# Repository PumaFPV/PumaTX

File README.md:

# PumaTX

THIS README IS NOT UP TO DATE

# Introduction:
This is a try to build my own FPV remote controller based on ESP32 (nRF52 later on) and DJI GL200A for its compactness and format.

# Release Candidates:

RC04: 
	Software:
		PPM
		SBus
		Hall Effect
		Pots reading (Left pot mode switch left = down ; Right = up ; RTH = overwrite)
		Arm reading
		Pre reading
		RTH reading
		Power on / off via sport switch
		basic screen use + vbat + splash screen
		
	Hardware:
		Micro USB (from controller)
		2S LiPo
		external RF (R9M)
		USB 2.0 (or 3.0 if I find one,) to plug in module (gnd, 5v, VBat, Tx)
		Support for JR module in phone holder
		
RC05:
	Software:
		Interupts for buttons (so code can run faster)
		MavLink (only rc, no telemetry) 
§		MavLink Bluetooth Passthrough (Uses to much memory, will have to sort it out for another release)
§		Choice between SBus and MavLink when compiling
		SoftPower use only interrupt
§		LED for power
		
	Hardware:
§		1S battery + USB charger + boost converter
§		MavLink module
		
RC06:
	Software:
		Menu Navigation
		
	Hardware:
		Turn on / off stuff (transistor & MOSFET)
		Fan
		Haptic
		
RC07:
	Software:
		Bluetooth HID
		
RC08:
	Software:
		MavLink telemetry screen

RC09:
	Software:
		CVBS Screen
		
	Hardware:
		USB 3.0 (5v, gnd, tx, rx, vid, 1, 2, VBat)
	
RC10:
	Hardware:
		Homemade PCB
		C1, C2
		Haptic
		
Other ideas:
	SPort
	FrSky X for bind / Rx num
	Sound output
	External bluetooth joystick
	Fix the calibration issue
	Remove screen loop
	eepron save
	
# Required specs:
-Read data from the hall effect MLX sensors from the controller

-Have 10 channels (can't do more cause of the limitation of the controller)

-Output SBus (to plug into R9M)

-Input SPort to read telemetry data (From R9M)

-Have a screen for minimal setup

-Have a Soft Power capabilty (using the power button from the controller)

This is the bare minimum. But I do have way more ideas coming.

# Folders:
In the "PumaTX_RC" folder you will find the different Release Candidate (Higher is better but could be unstable, read description for more details).

In the "Other" folder you will find different kind of "documentation" it is mostly here for my personnal use, as a reference.

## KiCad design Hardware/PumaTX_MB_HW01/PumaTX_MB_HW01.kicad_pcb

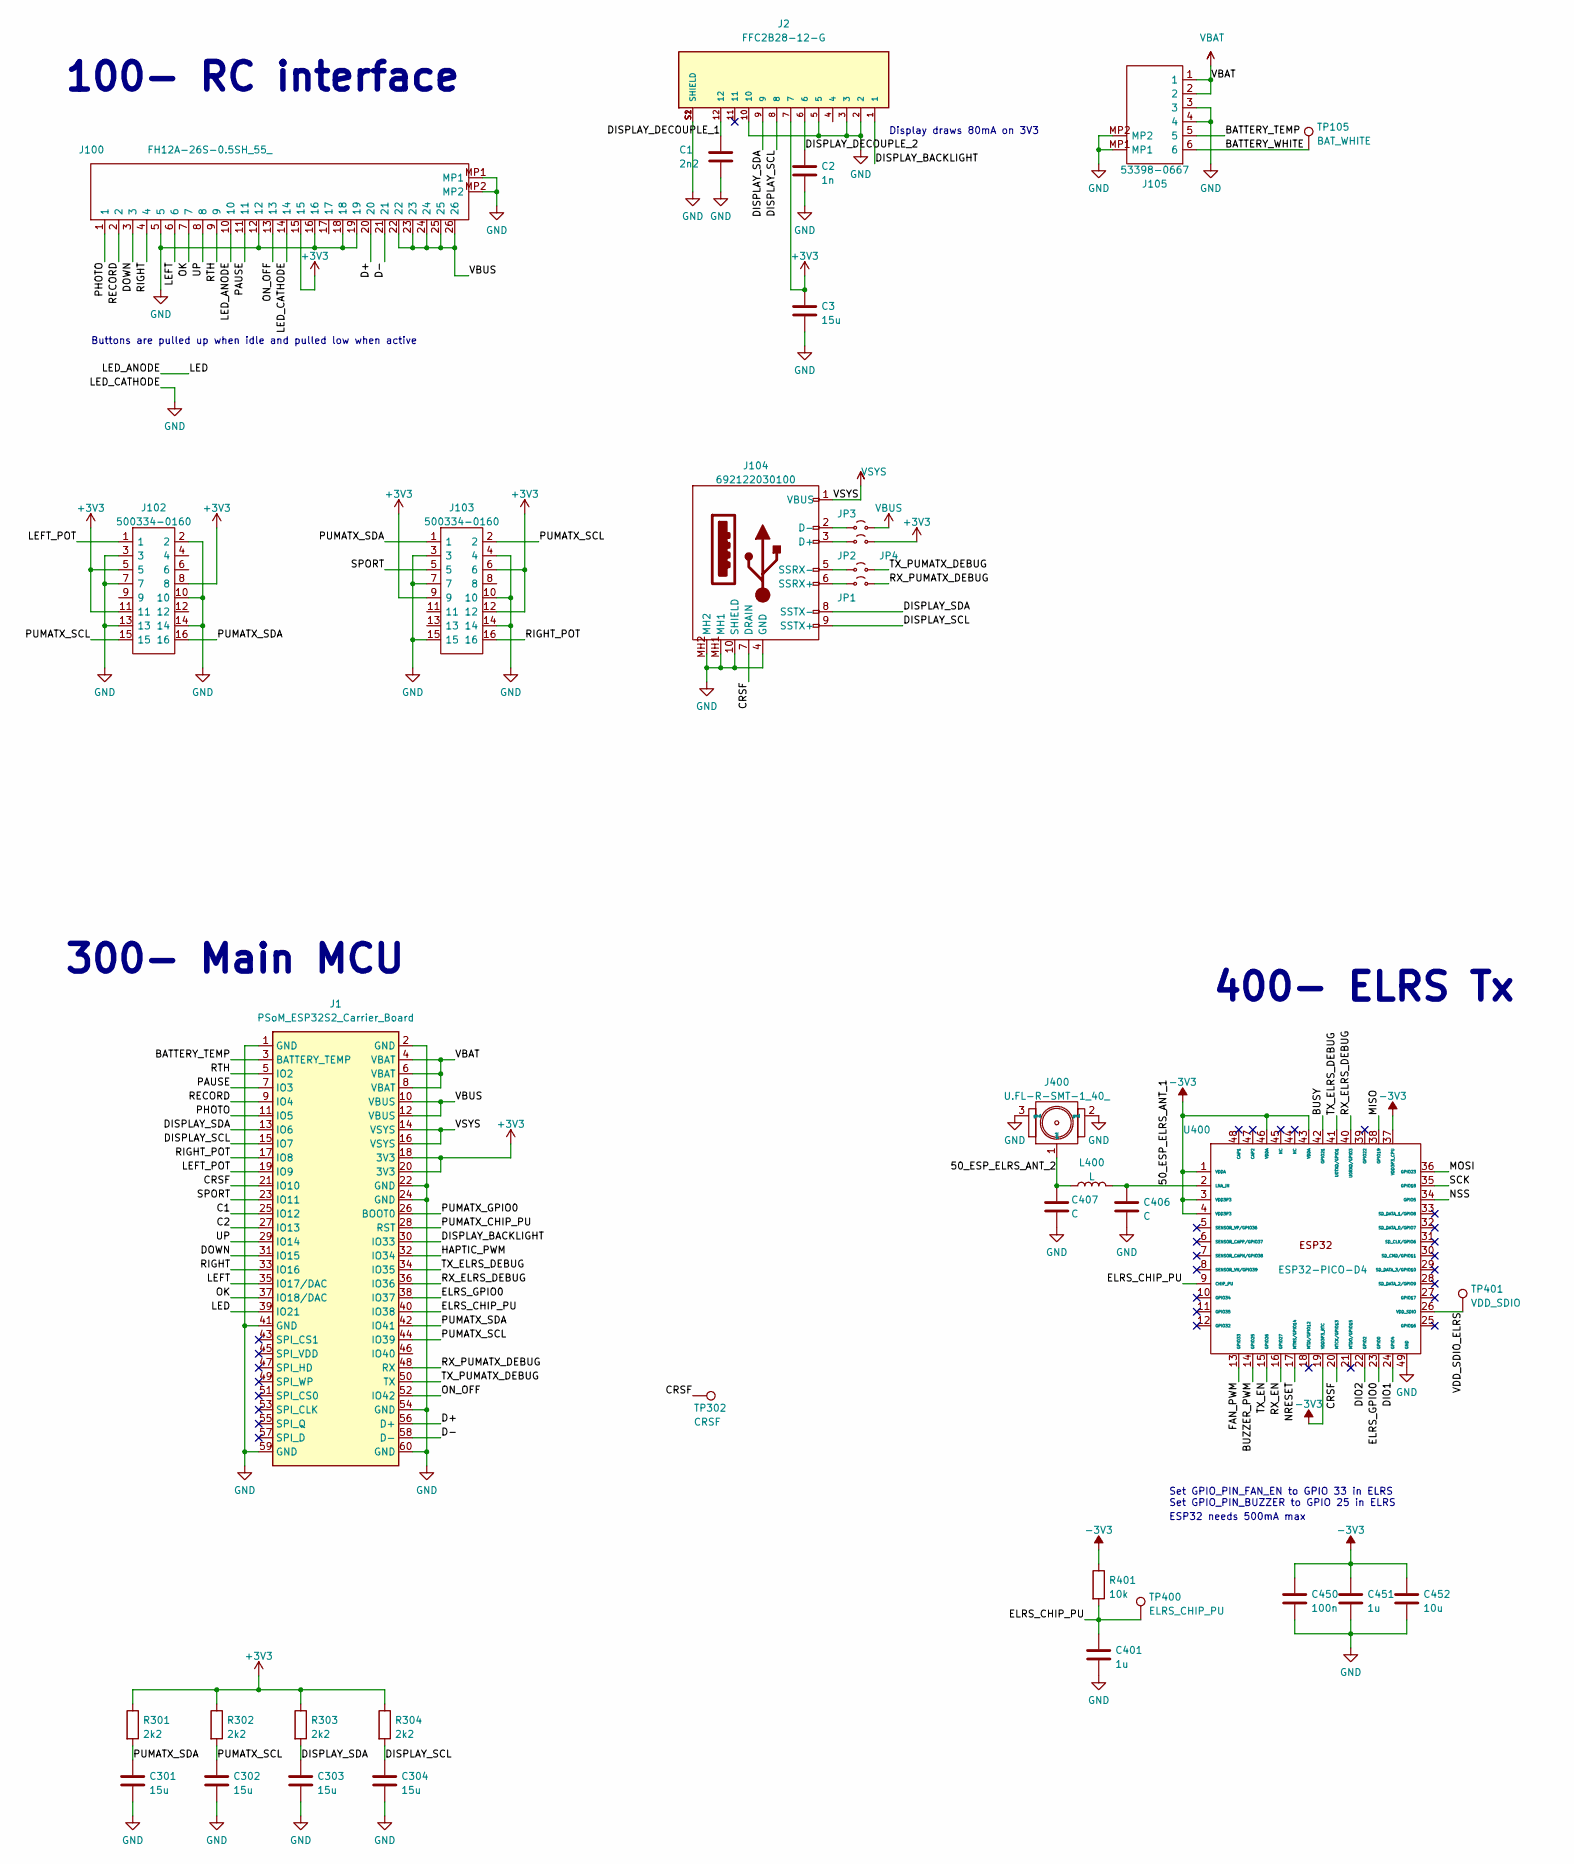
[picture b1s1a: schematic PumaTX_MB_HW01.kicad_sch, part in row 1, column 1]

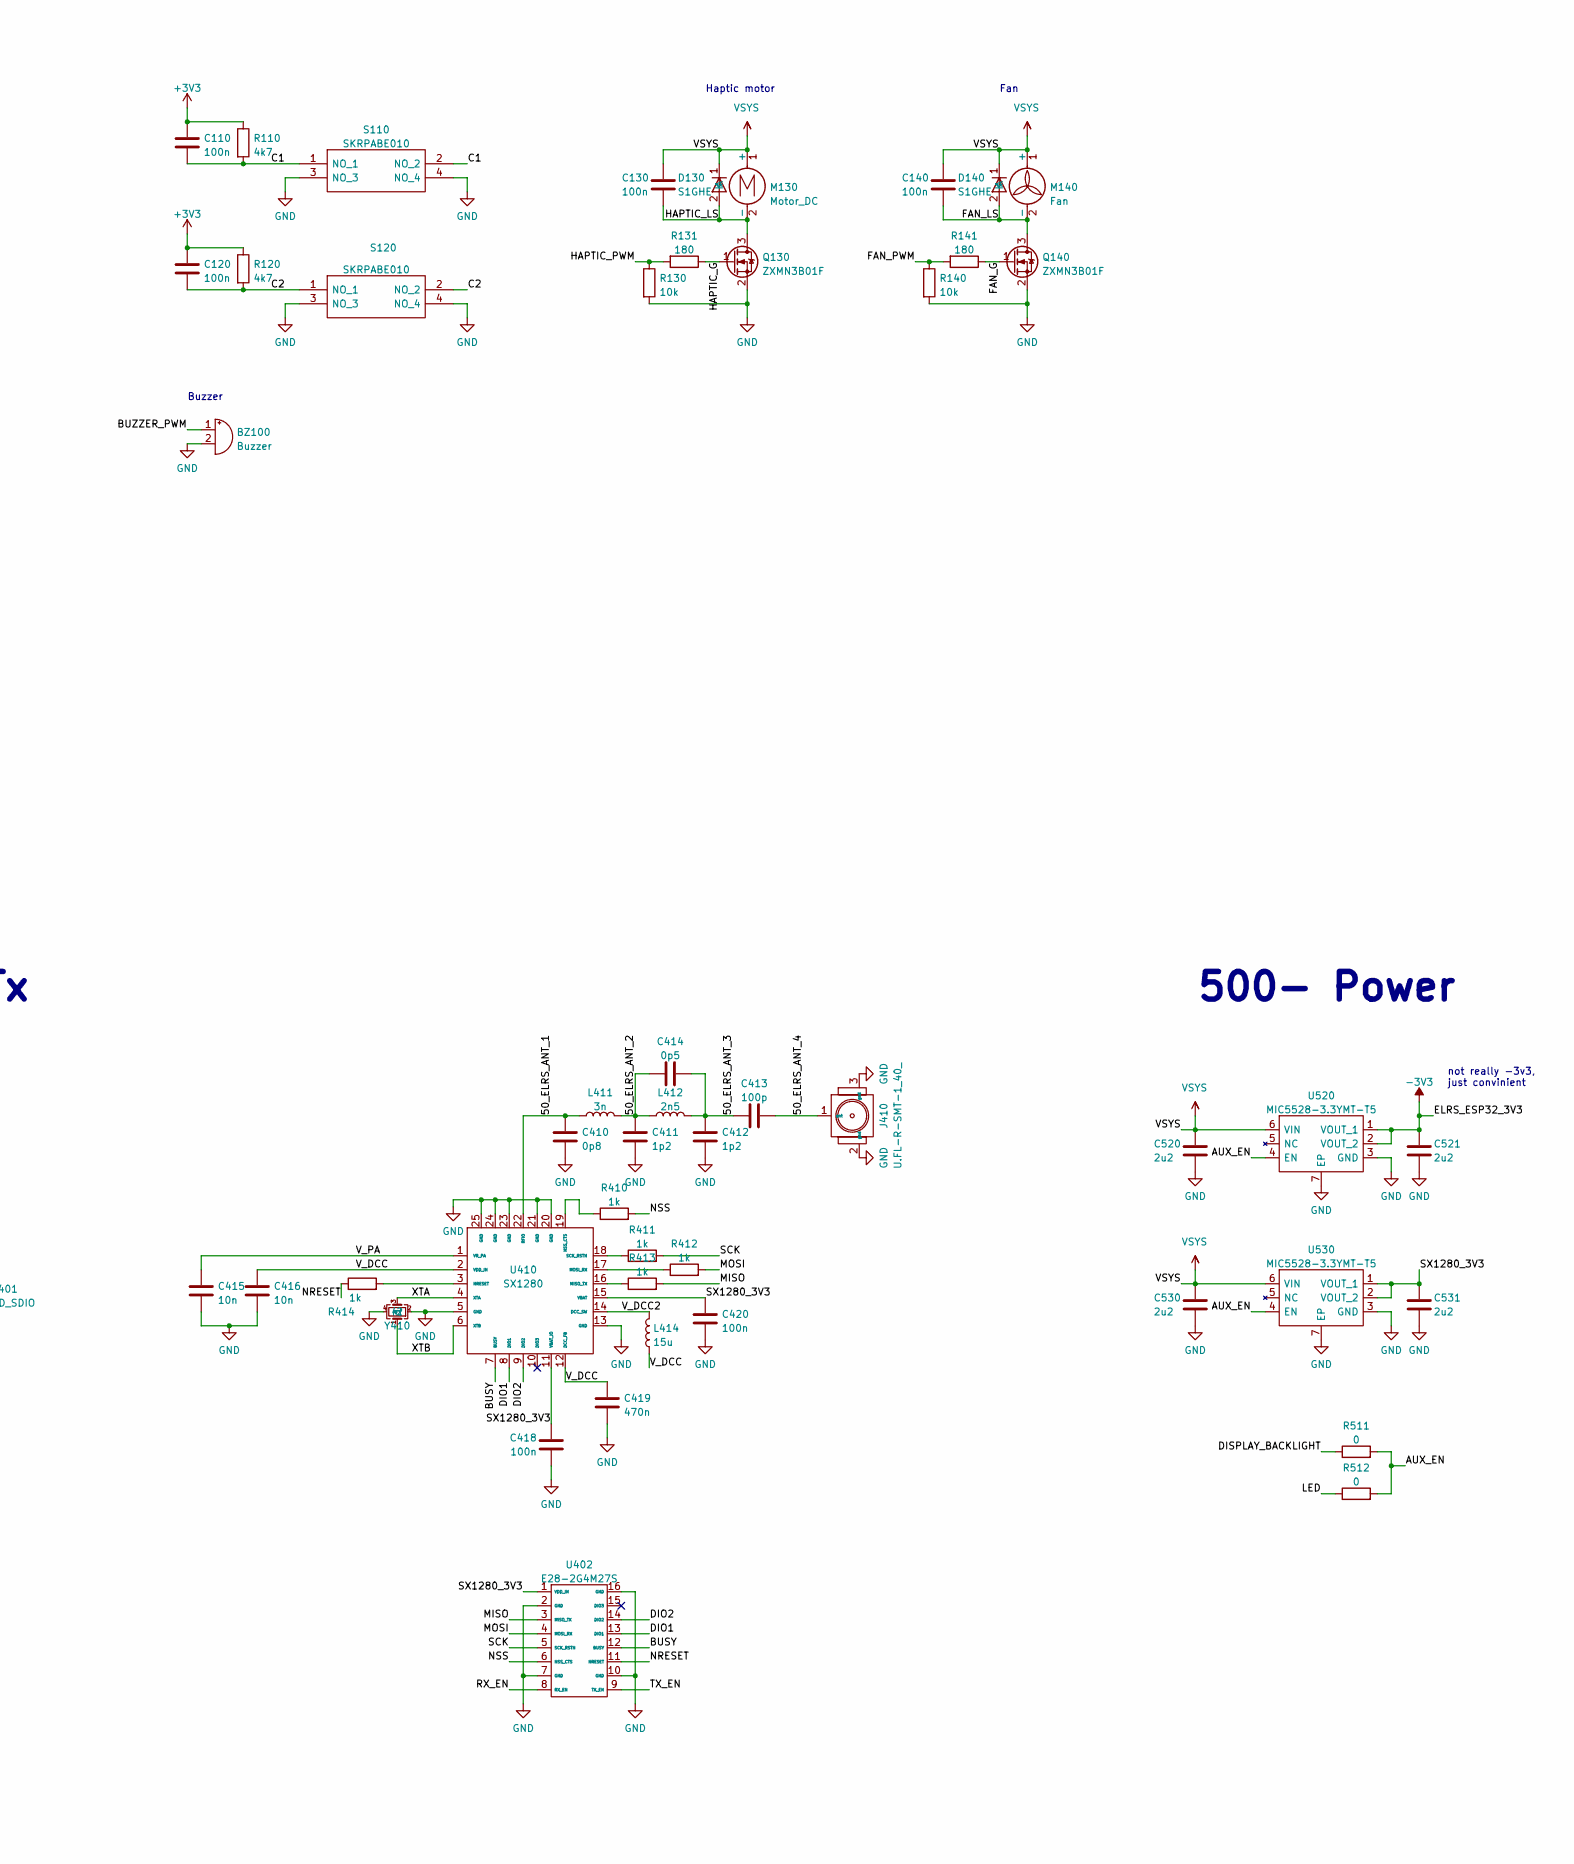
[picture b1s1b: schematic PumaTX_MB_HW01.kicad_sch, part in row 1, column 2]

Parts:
BZ100: Buzzer; GL200A_BUZZER
C1: 2n2; C_0402_1005Metric
C2: 1n; C_0402_1005Metric
C3, C301, C302, C303, C304: 15u; C_0402_1005Metric
C110, C120, C130, C140, C418, C420, C450: 100n; C_0402_1005Metric
C401, C451: 1u; C_0402_1005Metric
C406, C407: C; C_0201_0603Metric
C410: 0p8; C_0201_0603Metric
C411, C412: 1p2; C_0201_0603Metric
C413: 100p; C_0201_0603Metric
C414: 0p5; C_0201_0603Metric
C415, C416: 10n; C_0402_1005Metric
C419: 470n; C_0603_1608Metric
C452: 10u; C_0402_1005Metric
C520, C521, C530, C531: 2u2; C_0603_1608Metric
D130, D140: S1GHE; Mouser Part Number 512-S1GHE
J1: PSoM_ESP32S2_Carrier_Board; PSoM_ESP32S2_00
J2: FFC2B28-12-G; GCT_FFC2B28-12-G; PARTREV A; DigiKey_Part_Number 2073-FFC2B28-12-GTR-ND
J100: FH12A-26S-0.5SH_55_; FH12A26S05SH55; Mouser Part Number 798-FH12A-26S0.5SH55
J102, J103: 500334-0160; 5003340160; Mouser Part Number 538-500334-0160
J104: 692122030100; Mouser Part Number 710-692122030100
J105: 53398-0667; 533980667; Mouser Part Number 538-53398-0667
J400, J410: U.FL-R-SMT-1_40_; u.fl; Mouser Part Number 798-UFLRSMT140
JP1, JP2, JP3, JP4: Jumper_2_Small_Open; SolderJumper-2_P1.3mm_Open_RoundedPad1.0x1.5mm
L400: L; C_0402_1005Metric
L411: 3n; C_0402_1005Metric
L412: 2n5; C_0402_1005Metric
L414: 15u; C_0805_2012Metric
M130: Motor_DC; GL200A_HAPTIC_MOTOR
M140: Fan; SM02B-SURS-TF
Q130, Q140: ZXMN3B01F; SOT-23
R110, R120: 4k7; C_0402_1005Metric
R130, R140: 10k; C_0402_1005Metric
R131, R141: 180; C_0402_1005Metric
R301, R302, R303, R304: 2k2; C_0201_0603Metric
R401: 10k; C_0201_0603Metric
R410, R411, R412, R413, R414: 1k; C_0201_0603Metric
R511, R512: 0; C_0201_0603Metric
S110, S120: SKRPABE010; Mouser Part Number 688-SKRPAB
TP105: BAT_WHITE; TestPoint_Pad_D1.0mm
TP302: CRSF; TestPoint_Pad_D1.0mm
TP400: ELRS_CHIP_PU; TestPoint_Pad_D1.0mm
TP401: VDD_SDIO; TestPoint_Pad_D1.0mm
U400: ESP32-PICO-D4; ESP32-PICO-D4_1; Mouser Part Number 356-ESP32-PICO-D4
U402: E28-2G4M27S
U410: SX1280; QFN50P400X400X100-25N-D
U520, U530: MIC5528-3.3YMT-T5; SON40P120X120X60-7N-D; Mouser Part Number 998-MIC5528-3.3YMTT5
Y410: NX2016SA-52MHZ-EXS00A-CS06016; NX2016SA32MEXS00ACS06465; Mouser Part Number NX2016SA-52MHZ-EXS00A-CS06016

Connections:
+3V3: C3.1, C110.1, C120.1, J1.18 (3V3), J1.20 (3V3), J2.7, J100.15, J102.5, J102.8, J102.11, J103.6, J103.9, J103.12, JP4.2 (B), R110.1, R120.1, R301.1, R302.1, R303.1, R304.1; also elsewhere on the board
-3V3: C450.1, C451.1, C452.1, C521.1, R401.1, U400.1 (VDDA), U400.3 (VDD3P3), U400.4 (VDD3P3), U400.19 (VDD3P3_RTC), U400.37 (VDD3P3_CPU), U400.43 (VDDA), U400.46 (VDDA), U520.1 (VOUT_1), U520.2 (VOUT_2)
/50_ELRS_ANT_1: C410.1, L411.1, U410.22 (RFIO)
/50_ELRS_ANT_2: C411.1, C414.1, L411.2, L412.1
/50_ELRS_ANT_3: C412.1, C413.1, C414.2, L412.2
/50_ELRS_ANT_4: C413.2, J410.1 (ant)
/50_ESP_ELRS_ANT_1: C406.1, L400.2, U400.2 (LNA_IN)
/50_ESP_ELRS_ANT_2: C407.1, J400.1 (ant), L400.1
/AUX_EN: R511.2, R512.2, U520.4 (EN), U530.4 (EN)
/BATTERY_TEMP: J1.3 (BATTERY_TEMP), J105.5
/BATTERY_WHITE: J105.6, TP105.1
/BUSY: U400.42 (GPIO21), U402.12 (BUSY), U410.7 (BUSY)
/BUZZER_PWM: BZ100.1 (-), U400.14 (GPIO25)
/C1: C110.2, J1.25 (IO12), R110.2, S110.1 (NO), S110.2 (NO)
/C2: C120.2, J1.27 (IO13), R120.2, S120.1 (NO), S120.2 (NO)
/CRSF: J1.21 (IO10), J104.7 (DRAIN), TP302.1, U400.20 (MTCK/GPIO13)
/D+: J1.56 (D+), J100.20; also elsewhere on the board
/D-: J1.58 (D-), J100.21; also elsewhere on the board
/DIO1: U400.24 (GPIO4), U402.13 (DIO1), U410.8 (DIO1)
/DIO2: U400.22 (GPIO2), U402.14 (DIO2), U410.9 (DIO2)
/DISPLAY_BACKLIGHT: J1.30 (IO33), J2.1, R511.1
/DISPLAY_DECOUPLE_1: C1.1, J2.12; also elsewhere on the board
/DISPLAY_DECOUPLE_2: C2.1, J2.6; also elsewhere on the board
/DISPLAY_SCL: C304.1, J1.15 (IO7), J2.8, J104.9 (SSTX+), R304.2
/DISPLAY_SDA: C303.1, J1.13 (IO6), J2.9, J104.8 (SSTX-), R303.2
/DOWN: J1.31 (IO15), J100.3; also elsewhere on the board
/ELRS_CHIP_PU: C401.1, J1.40 (IO38), R401.2, TP400.1, U400.9 (CHIP_PU)
/ELRS_GPIO0: J1.38 (IO37), U400.23 (GPIO0)
/FAN_G: Q140.1 (G), R141.1
/FAN_LS: C140.1, D140.2 (A), M140.2 (-), Q140.3 (D)
/FAN_PWM: R140.1, R141.2, U400.13 (GPIO33)
/HAPTIC_G: Q130.1 (G), R131.1
/HAPTIC_LS: C130.1, D130.2 (A), M130.2 (-), Q130.3 (D)
/HAPTIC_PWM: J1.32 (IO34), R130.1, R131.2
/LED: J1.39 (IO21), J100.10, R512.1; also elsewhere on the board
/LEFT: J1.35 (IO17/DAC), J100.6; also elsewhere on the board
/LEFT_POT: J1.19 (IO9), J102.1
/MISO: R413.2, U400.38 (GPIO19), U402.3 (MISO_TX)
/MOSI: R412.2, U400.36 (GPIO23), U402.4 (MOSI_RX)
/NRESET: R414.1, U400.17 (MTMS/GPIO14), U402.11 (NRESET)
/NSS: R410.2, U400.34 (GPIO5), U402.6 (NSS_CTS)
/OK: J1.37 (IO18/DAC), J100.7; also elsewhere on the board
/ON_OFF: J1.52 (IO42), J100.13; also elsewhere on the board
/PAUSE: J1.7 (IO3), J100.11; also elsewhere on the board
/PHOTO: J1.11 (IO5), J100.1; also elsewhere on the board
/PUMATX_CHIP_PU: J1.28 (RST)
/PUMATX_GPIO0: J1.26 (BOOT0)
/PUMATX_SCL: C302.1, J1.44 (IO39), J102.15, J103.2, R302.2
/PUMATX_SDA: C301.1, J1.42 (IO41), J102.16, J103.1, R301.2
/RECORD: J1.9 (IO4), J100.2; also elsewhere on the board
/RIGHT: J1.33 (IO16), J100.4; also elsewhere on the board
/RIGHT_POT: J1.17 (IO8), J103.16
/RTH: J1.5 (IO2), J100.9; also elsewhere on the board
/RX_ELRS_DEBUG: J1.36 (IO36), U400.40 (U0RXD/GPIO3)
/RX_EN: U400.16 (GPIO27), U402.8 (RX_EN)
/RX_PUMATX_DEBUG: J1.48 (RX), JP1.2 (B)
/SCK: R411.2, U400.35 (GPIO18), U402.5 (SCK_RSTN)
/SPORT: J1.23 (IO11), J103.5
/SX1280_3V3: C418.1, C420.1, C531.1, U402.1 (VDD_IN), U410.11 (VBAT_IO), U410.15 (VBAT), U530.1 (VOUT_1), U530.2 (VOUT_2)
/TX_ELRS_DEBUG: J1.34 (IO35), U400.41 (U0TXD/GPIO1)
/TX_EN: U400.15 (GPIO26), U402.9 (TX_EN)
/TX_PUMATX_DEBUG: J1.50 (TX), JP2.2 (B)
/UP: J1.29 (IO14), J100.8; also elsewhere on the board
/VBAT: J1.4 (VBAT), J1.6 (VBAT), J1.8 (VBAT), J105.1, J105.2
/VDD_SDIO_ELRS: TP401.1, U400.26 (VDD_SDIO)
/VSYS: C130.2, C140.2, C520.1, C530.1, D130.1 (K), D140.1 (K), J1.14 (VSYS), J1.16 (VSYS), J104.1 (VBUS), M130.1 (+), M140.1 (+), U520.6 (VIN), U530.6 (VIN)
/V_DCC: C416.1, C419.1, L414.1, U410.2 (VDD_IN), U410.12 (DCC_FB)
/V_DCC2: L414.2, U410.14 (DCC_SW)
/V_PA: C415.1, U410.1 (VR_PA)
/XTA: U410.4 (XTA), Y410.3
/XTB: U410.6 (XTB), Y410.1
GND: BZ100.2 (+), C1.2, C2.2, C3.2, C301.2, C302.2, C303.2, C304.2, C401.2, C406.2, C407.2, C410.2, C411.2, C412.2, C415.2, C416.2, C418.2, C419.2, C420.2, C450.2, C451.2, C452.2, C520.2, C521.2, C530.2, C531.2, J1.1 (GND), J1.2 (GND), J1.22 (GND), J1.24 (GND), J1.41 (GND), J1.54 (GND), J1.59 (GND), J1.60 (GND), J2.2, J2.3, J2.5, J2.10, J2.S1 (SHIELD), J2.S2 (SHIELD), J100.5, J100.12, J100.14, J100.16, J100.18, J100.19, J100.MP1, J100.MP2, J102.2, J102.3, J102.7, J102.10, J102.13, J102.14, J103.3, J103.4, J103.7, J103.10, J103.14, J103.15, J104.4 (GND), J104.10 (SHIELD), J104.MH1, J104.MH2, J105.3, J105.4, J105.MP1, J105.MP2, J400.2 (gnd), J400.3 (gnd), J410.2 (gnd), J410.3 (gnd), Q130.2 (S), Q140.2 (S), R130.2, R140.2, S110.3 (NO), S110.4 (NO), S120.3 (NO), S120.4 (NO), U400.49 (GND), U402.2 (GND), U402.7 (GND), U402.10 (GND), U402.16 (GND), U410.5 (GND), U410.13 (GND), U410.20 (GND), U410.21 (GND), U410.23 (GND), U410.24 (GND), U410.25 (GND), U520.3 (GND), U520.7 (EP), U530.3 (GND), U530.7 (EP), Y410.2, Y410.4; also elsewhere on the board
unnamed: J104.3 (D+), JP4.1 (A)
unnamed: J104.2 (D-), JP3.1 (A)
unnamed: J104.6 (SSRX+), JP1.1 (A)
unnamed: J104.5 (SSRX-), JP2.1 (A)
unnamed: R413.1, U410.16 (MISO_TX)
unnamed: R412.1, U410.17 (MOSI_RX)
unnamed: R414.2, U410.3 (NRESET)
unnamed: R410.1, U410.19 (NSS_CTS)
unnamed: R411.1, U410.18 (SCK_RSTN)
VBUS: J1.10 (VBUS), J1.12 (VBUS), J100.22, J100.23, J100.24, J100.25, J100.26, JP3.2 (B); also elsewhere on the board

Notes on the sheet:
Buzzer
Fan
not really -3v3, just convinient
Display draws 80mA on 3V3
300- Main MCU
100- RC interface
500- Power
400- ELRS Tx
Haptic motor
Buttons are pulled up when idle and pulled low when active
Set GPIO_PIN_FAN_EN to GPIO 33 in ELRS Set GPIO_PIN_BUZZER to GPIO 25 in ELRS
ESP32 needs 500mA max

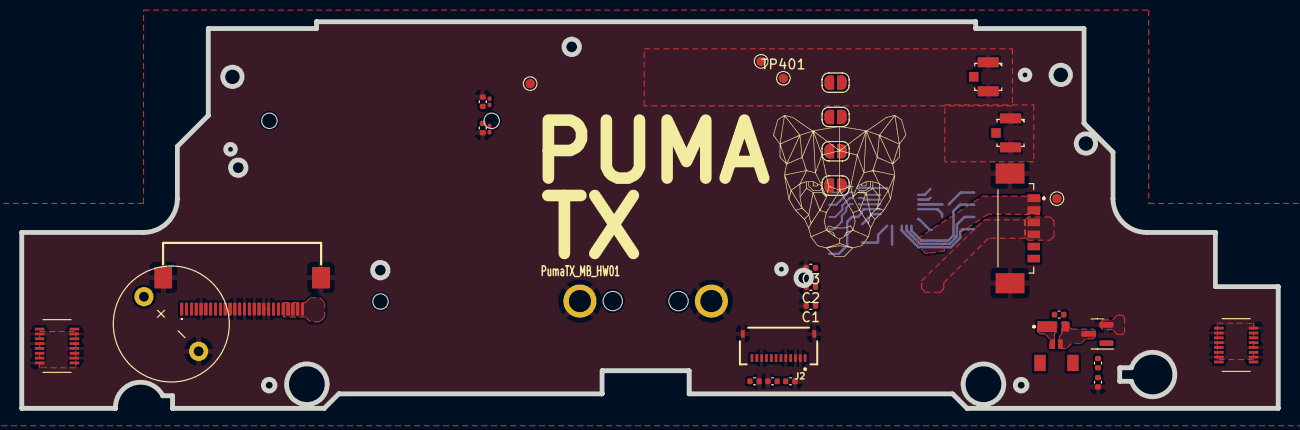
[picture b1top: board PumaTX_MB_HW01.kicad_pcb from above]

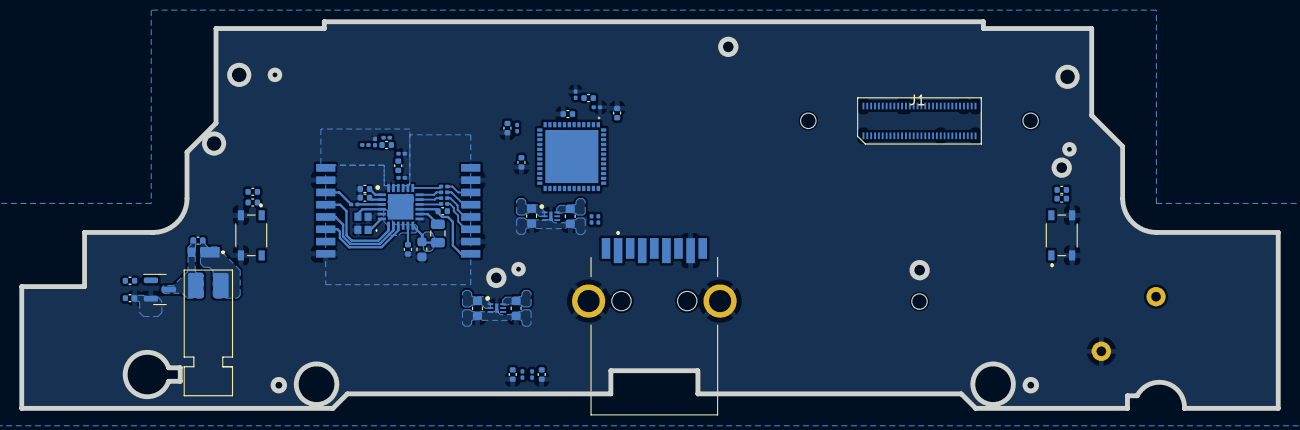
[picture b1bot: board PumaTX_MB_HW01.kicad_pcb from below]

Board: 4 copper layers, 130.0 x 40.0 mm, 89 parts (56 on the bottom side), 80 nets.

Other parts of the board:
C101: 2n2; C_0402_1005Metric
C102: 1n; C_0402_1005Metric
C103: 15u; C_0402_1005Metric
J100#2: FH12A-26S-0.5SH_55_; FH12A26S05SH55

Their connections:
+3V3: C103.1, J100#2.15; also elsewhere on the board
/D+: J100#2.20; also elsewhere on the board
/D-: J100#2.21; also elsewhere on the board
/DISPLAY_DECOUPLE_1: C101.1; also elsewhere on the board
/DISPLAY_DECOUPLE_2: C102.1; also elsewhere on the board
/DOWN: J100#2.3; also elsewhere on the board
/LED: J100#2.10; also elsewhere on the board
/LEFT: J100#2.6; also elsewhere on the board
/OK: J100#2.7; also elsewhere on the board
/ON_OFF: J100#2.13; also elsewhere on the board
/PAUSE: J100#2.11; also elsewhere on the board
/PHOTO: J100#2.1; also elsewhere on the board
/RECORD: J100#2.2; also elsewhere on the board
/RIGHT: J100#2.4; also elsewhere on the board
/RTH: J100#2.9; also elsewhere on the board
/UP: J100#2.8; also elsewhere on the board
GND: C101.2, C102.2, C103.2, J100#2.5, J100#2.12, J100#2.14, J100#2.16, J100#2.18, J100#2.19, J100#2.MP1, J100#2.MP2; also elsewhere on the board
VBUS: J100#2.22, J100#2.23, J100#2.24, J100#2.25, J100#2.26; also elsewhere on the board

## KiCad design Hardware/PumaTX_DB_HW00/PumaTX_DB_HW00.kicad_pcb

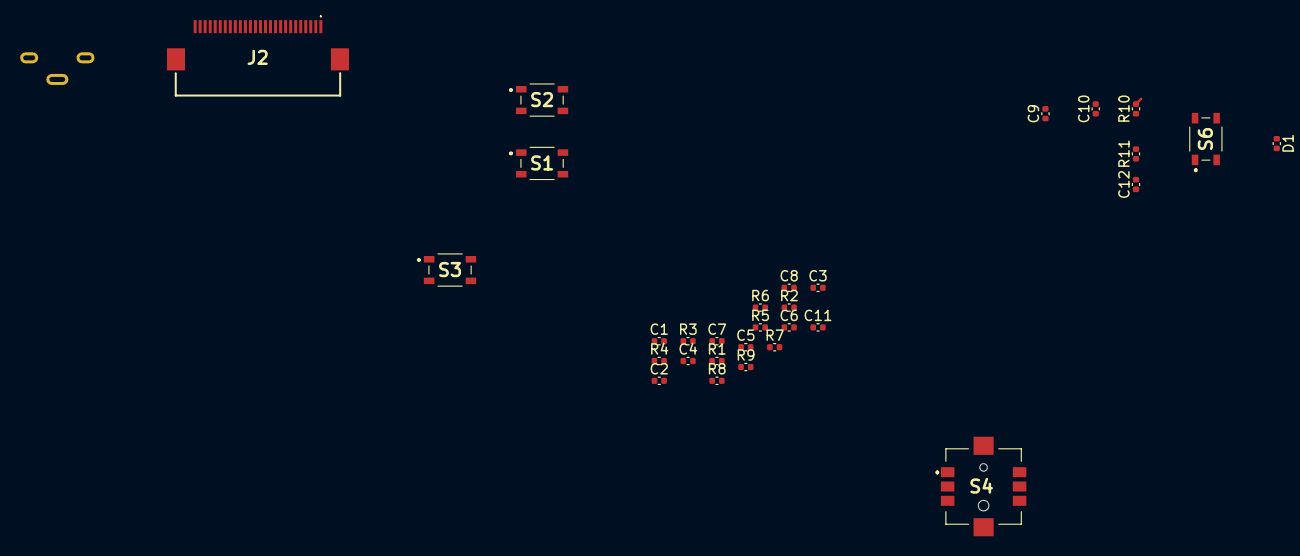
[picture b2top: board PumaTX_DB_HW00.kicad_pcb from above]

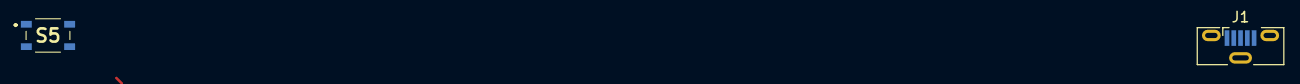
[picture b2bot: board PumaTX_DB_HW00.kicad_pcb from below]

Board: 2 copper layers, 32 parts (2 on the bottom side), 2 nets.

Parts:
C1, C2, C3, C4, C5, C6, C7, C8, C9, C10, C11, C12: C; C_0402_1005Metric
D1: LED; C_0402_1005Metric
J1: USB_B_Micro; USB_Micro-B_Molex-105133-0001
J2: FH12A-26S-0.5SH_55_; FH12A26S05SH55
R1, R2, R3, R4, R5, R6, R7, R8, R9: R; C_0402_1005Metric
R10: 1k1; C_0402_1005Metric
R11: 11; C_0402_1005Metric
S1, S2, S3, S5, S6: SKRPABE010
S4: SKRHABE010

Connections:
GND: J2.5, J2.12, J2.16, J2.18, J2.19, J2.MP1, J2.MP2, S1.3 (NO_3), S2.3 (NO_3), S3.1 (NO_1), S4.5 (COMMON), S5.3 (NO_3)
VBUS: J2.22, J2.23, J2.24, J2.25, J2.26

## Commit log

2019-05-22 removed useless file
2019-05-22 Added compile error to help debug
2019-05-22 Fixed some bugs
2019-05-22 Trying to fixe lib issue
2019-05-22 Still trying to fix the lib
2019-05-22 One last problem before something might work
    "multiple definition of"
    For more detail check: Compiling error.txt
2019-05-22 Done! Compiles has to be tested
2019-05-23 MLX lib properly done, choose address for left and right
    Next step support screen and test RC03
2019-05-23 added support for sh1106
2019-05-23 Display not working
    appears to be a refresh problem
2019-05-23 Went back to U8g2 Lib for screen but still no display
    Need to fix u8g2 to make screen work (maybe conflict with mlx?)
2019-05-23 Got the screen working
    need to fix the startup bmp
2019-05-23 Screen is working
    need to fix delay of navigation switch
2019-05-23 Made a short description of the project
2019-05-25 Done with RC03 SBus is working
2019-05-25 Beginning of RC04
    Goals:
    -Buttons:
    -Read nav joystick capacity
    -Add 6 channels from buttons and pots
    -Add SoftPower
2019-05-25 Added OTA back
2019-05-28 RC04 updated for gl200a pcb
    added joystick for nav, buttons (all but c1 & c2)
2019-05-29 added "rs latch" to arm and rth
2019-06-04 late update don't know what changed
2019-06-11 added mavlink doc for futur implementation
2019-06-11 no change to code
2019-06-13 Started Soft power code in button.h
2019-06-13 Started some big changes in code design
    added .h files to clarify code
2019-06-18 Code compiles, not tested yet on hardware
2019-06-19 removed bind option for X modules
2019-06-19 added compile choice between sbus and mavlink
2019-06-19 Need to fix soft power, doesn't work
2019-06-20 cleaned master sources
2019-06-20 added master opentx
2019-06-26 trying to add softpower but not easy
2019-07-10 Updated the release candidate guide
2019-07-12 Made some minor changes
    done the left pot mode switch
2019-07-17 RC05 Started
2019-07-19 MavLink should work by now
2019-07-20 working on softpower
2019-08-02 working on the hardware of RC04
    too much latency, trying to figure it out
2019-08-14 fixing the mlx problem on esp32 (RC04)
2019-08-22 trying to figure out some problem with SBus
    Added simple PPM version to make sure mlx was working
    Finally fixed the MLX issue on ESP32 (if data>60000 then data = data - 60000) easy fix, seems to work fine though
2019-08-22 Fixed RC04
2019-12-26 started a new branch to accomodate dualcore
2020-03-03 PXX is the way to go for R9M
2020-10-22 Actually using an Arduino pro mini to create PXX
2020-10-22 updated dual core version
2020-11-03 PXX generated by esp32 is almost there
2020-11-03 working on pxx in pumatx_32 problem with put_pcm_byte()
    dualcore version isnt working yet
2020-11-04 PXX works!!!
2020-11-04 PXX works!!!
    code is in PumaTX_32
    some cleaning is required but it is good for now!
2020-11-04 code is cleanner now
2020-11-05 Started PumaTX_32 branch
    PumaTX_32_RC04 is done, basic PXX is working.
    RC05 goal is to not break it and add dual core usage
2020-11-08 removed digitalRead for esp32 specific commands
2020-11-08 started to think about custom radio module sx1280
2020-11-20 started reverse engineering the mavic controller dispaly
2020-11-20 used for
2020-11-20 figuring out which bit turns on which part of the display
2020-11-23 added scroll function for the 11 14 segments display
2020-11-23 everything is working pretty well
    set_text() and set_name() need optimisation for scrolling text while not freezing the rest of the screen
2020-11-23 surprise
2020-12-02 added pumatx32_RC4.1
    pumatx32_RC4.1 is a version where the display and mlx libs have been added and tested
2020-12-02 made some small adjustements to rcdata in pumatx32_RC4.1
2020-12-05 Starting RC05
    RC04.1 added display and mlx libs.
    Both are working, only delay between pxx pulses have been increased: solution: dualcore -> going on RC05 for dualcore functionnality
2021-01-07 started doing a pptx to organize the code
2021-01-27 Fixed some bugs with the display
    The display seems to be loosing connection sometimes, so re initialising the library seems to be a quick fix. (calling display.begin each time to update it)
    Don't know if the issue is on hardware side or softare side
    I tried with a new display and ribbon plug (FPC 12P 0.5mm)
2021-02-01 remade file organisation for better use of vs code git functionnality
2021-02-01 added elrs
2021-02-01 little change to comment
2021-09-12 Back to the project, added HSIS
    Changes to be committed:
    modified: Other/_Master Program for sourcing code/ExpressLRS-master/src/src/tx_main.cpp
    modified: old/PumaTX_display/PumaTX_display.ino
    modified: old/PumaTX_display/display.cpp
    modified: old/PumaTX_display/display.h
    modified: platformio.ini
2021-09-12 modified: README.md
2021-09-13 made changes to dualcore functions
2021-09-13 removed a lot of useless files
2021-09-13 new file: Organisation/ESP32 HSIS.xlsx
2021-09-13 added files (doc, orga, old, pcb, test)
2021-09-14 fixed dualcore no delay
2021-09-16 Started aading components schematics to PumaTX KiCAD's library
2021-09-17 added EMH3 dual transistor schematic's to pumalib
2021-09-17 added flash chip W25Q32JVZPIQ to puma lib
2021-09-21 added components to pumalib
2021-09-22 changed organisation new file: pcb/datasheet/ESP32/esp32_datasheet_en.pdf new file: pcb/datasheet/ESP32/esp32_hardware_design_guidelines_en.pdf new file: pcb/datasheet/ESP32/esp32_technical_reference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
2021-09-22 modified: pcb/Tx_mother_board/Tx_mother_board/PumaTx.dcm modified: pcb/Tx_mother_board/Tx_mother_board/PumaTx.lib new file: pcb/datasheet/AP7343Q.pdf new file: pcb/datasheet/esp32_datasheet_en.pdf
2021-09-23 added new component to kicad lib
2022-05-23 Working a bit on the schematic
2022-07-07 Finally, the real schematic is coming
2022-07-10 Updated folder structure
2022-07-10 Added E28-2G4M27S
2022-07-13 Small updates around SX1280
2022-07-16 Updated schematic
2022-07-16 Updated schematics
2022-07-18 Started a rough layout
2022-07-20 Started working on the power part
2022-07-20 Started pinout of button flex
2022-07-20 quick schematic update
2022-07-20 Flex pinout added to schematic
2022-07-20 Added some footprints
2022-07-25 small updates
2022-07-25 Added display consumption
2022-07-25 Minor updates
2022-07-28 Changed motor and fan schematics
2022-07-29 Finished BQ, EPS32 integration
2022-07-29 Added pptx of PCBs analysis
2022-07-30 Almost done!
2022-08-01 Schematic is "done"
    Functionaly it is done, but could get some cleanup
2022-08-04 started some software tests
2022-08-04 looking at simpleTX CRSF implementation
2022-08-04 cleanup of schematic
2022-08-07 Added license
2022-08-07 quick folder organisation modification
2022-08-08 cleanup
2022-08-11 Generated BOM and changed 2 capa footprints
2022-08-11 updated bom
2022-08-12 newer backup
2022-08-17 PCB layout is done, routing to go!
2022-08-17 quick layout update
2022-08-18 added mouser cart
2022-08-18 Started layout
2022-08-18 updated layout
2022-08-22 Continued routing
2022-09-07 quick esp32 update
2022-09-12 working on routing / placement
2022-09-13 Quick update
2022-09-13 Routing update
2022-09-14 Done SX1280 routing and half of RF
2022-09-14 routing is ongoing
2022-09-15 rf backup
2022-09-15 some changes on routing, every QFN is on the same side
2022-09-16 Routing goes on and on and on...
2022-09-17 and on and on and on... It is getting harder
2022-09-18 Wow its gonna be complicated
2022-09-19 Almost done !! only 3 PSU to go
2022-09-19 Is this the end? or is it just the beginning?
2022-09-19 Order done. Is it a mistake? maybe...
2022-09-22 Lets go for software
2022-09-25 started working on configurator
2022-09-26 quick tries on objectifying I2C class or something like that
2022-09-26 GUI working (lol no)
2022-09-27 small corrections
2022-09-28 Updated mlx and display lib to input i2c object
2022-09-28 it builds!!!
2022-10-05 software fix
2022-10-05 Fixed I2C error, display bus wasnt initialized
2022-10-05 changed function timing
2022-10-06 added more detail about gpio requierment
2022-10-06 created PUMATX_MB_HW01 and added patch to HW00
2022-10-06 hw01
2022-10-09 button bringup
2022-10-09 button bringup 2
2022-10-10 Button and battery bringup done
2022-10-11 haptic bringup done / DB_HW00 started
2022-10-11 I2C scanner added
2022-10-13 mlx i2c is working
2022-10-13 MLX data seems all good, need to try with gimbals. Channel data is good
2022-10-16 preliminary work on crsf integration
2022-10-17 Display works <3
2022-10-19 Battery reading is shown on display
2022-10-19 Menu navigation is working ✅
2022-10-19 display I2C clock at 1MHz
2022-10-19 quick comment
2022-10-19 Display refresh optimisation
2022-10-20 display optimisation, down to 118us/loop
2022-10-20 updated navigation menu
2022-10-20 display string on 7 segment
2022-10-20 Added function management
2022-10-22 added inBetweenTime
2022-10-22 inBetweenTime added
2022-10-23 function's telemetry was a mess, did some cleanup
2022-10-23 added haptic function
2022-10-23 small cahnges
2022-10-25 trying to add crsf
2022-10-25 lol fixed yesterday issue
2022-10-25 started working on display.off(0b000); feature
2022-10-31 code cleanup
2023-03-08 moved mecha parts to folder
2025-01-13 MB_00 schematic done
2025-01-15 added comments to main.cpp
2025-01-16 just a test
2025-01-18 updated display connector
2025-01-25 cleaning
2025-03-02 worked on mb_01 schematic
2025-04-02 started schematics of LR1121
2026-05-28 Converted solidworks files to STEP
